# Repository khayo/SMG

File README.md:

# SMG - Sistema de Monitoramento de Geradores

## Introdução

Projeto de conclusão de curso dos alunos do curso de eletroeletrônica da ETEC Lauro Gomes

## Integrantes
* Caio Pavan Lima dos Santos
* Guilheme Gil Farias Sousa
* Gustavo Vinícius de Oliveira Barros
* Khayo Vannucci Rodrigues
* Lucas Barros Silva

## Sobre o Projeto
Trata-se de um hardware de automação de geradores, tanto a parte física (placas e componente), quanto a parte lógica (software de controle) foram desenvolvidas por nós.

## Microcontrolado
Está sendo utilizadado o PIC18F4550, poís além de possuir uma grande quantidade de portas lógicas e alta velocidade de processamento (até 48mHz), possui suporte a comunicação USB, o que pode simplificar updates de Firmware no futuro.

## IDE
A IDE selecionada para desenvolver o projeto foi o MikroC devido a familiaridade dos membros com a ferramenta e a abundância de material disponível para consulta.

## Projeto Virtual
Para simulações está sendo utilizado o Software Proteus, também escolhido devido a familiaridade dos membros com a ferramenta.

## Projeto Físico
O Hardware está sendo desenvolvido em protoboard e após realização de testes de funcionamento, será montado em placa de circuito impresso.

## Monografia
Também está disponivel neste repositório a monografia, por onde mostraremos os passos do desenvolvimento do projeto.

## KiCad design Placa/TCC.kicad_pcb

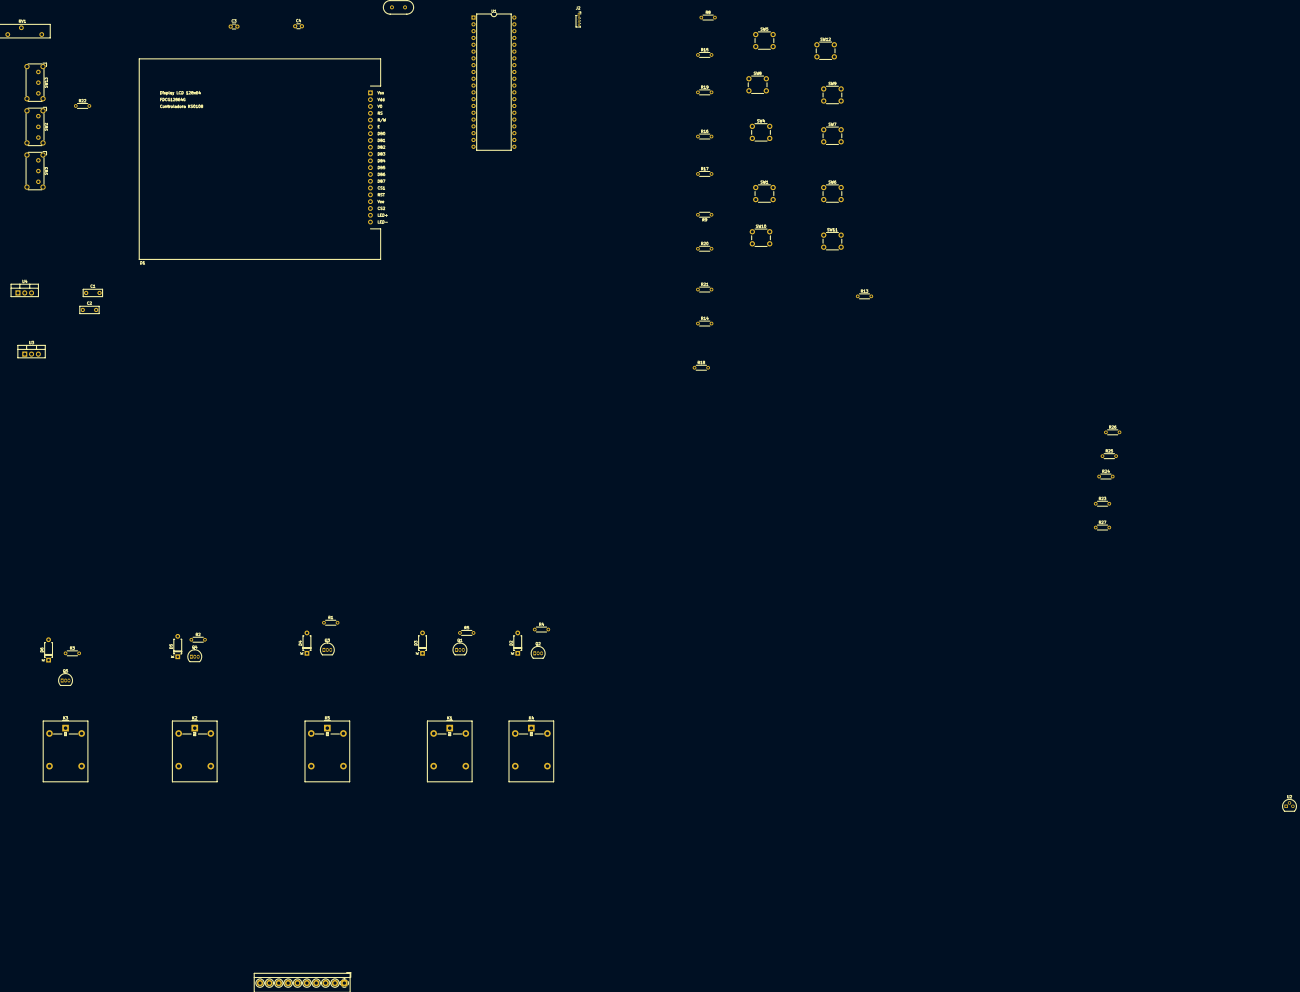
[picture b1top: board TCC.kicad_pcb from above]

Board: 2 copper layers, 63 parts (0 on the bottom side), 69 nets, no tracks yet.

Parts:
C1, C2: 10n; C_Rect_L7.0mm_W2.5mm_P5.00mm
C3, C4: 22p; C_Disc_D3.0mm_W1.6mm_P2.50mm
D1: FDCG12864; FDCG12864G
D2, D3, D4, D5, D6: DIODE; D_A-405_P7.62mm_Horizontal
J1: Screw_Terminal_01x10; TerminalBlock_4Ucon_1x10_P3.50mm_Horizontal
J2: Conn_01x05_Female; PinSocket_1x05_P1.00mm_Vertical
K1, K2, K3, K4, K5: G5LE-1; Relay_SPDT_Omron-G5LE-1
Q1, Q2, Q3, Q4, Q5: BC548; TO-92_Inline
R1, R2, R3, R4, R5, R16: 4700; R_Axial_DIN0204_L3.6mm_D1.6mm_P5.08mm_Horizontal
R8: 3300R; R_Axial_DIN0204_L3.6mm_D1.6mm_P5.08mm_Horizontal
R9: 2200R; R_Axial_DIN0204_L3.6mm_D1.6mm_P5.08mm_Horizontal
R13, R25, R26: 1000; R_Axial_DIN0204_L3.6mm_D1.6mm_P5.08mm_Horizontal
R14: 10000; R_Axial_DIN0204_L3.6mm_D1.6mm_P5.08mm_Horizontal
R15: 6800; R_Axial_DIN0204_L3.6mm_D1.6mm_P5.08mm_Horizontal
R17: 3900; R_Axial_DIN0204_L3.6mm_D1.6mm_P5.08mm_Horizontal
R18: 680; R_Axial_DIN0204_L3.6mm_D1.6mm_P5.08mm_Horizontal
R19: 470; R_Axial_DIN0204_L3.6mm_D1.6mm_P5.08mm_Horizontal
R20, R22: 220; R_Axial_DIN0204_L3.6mm_D1.6mm_P5.08mm_Horizontal
R21: 33; R_Axial_DIN0204_L3.6mm_D1.6mm_P5.08mm_Horizontal
R23: 100000; R_Axial_DIN0204_L3.6mm_D1.6mm_P5.08mm_Horizontal
R24: 33000; R_Axial_DIN0204_L3.6mm_D1.6mm_P5.08mm_Horizontal
R27: 27000; R_Axial_DIN0204_L3.6mm_D1.6mm_P5.08mm_Horizontal
RV1: R_POT; Potentiometer_Bourns_3006P_Horizontal
SW1, SW4, SW5, SW6, SW7, SW8, SW9, SW10, SW11, SW12: SW_Push_Dual; SW_PUSH_6mm_2_Contatos
SW2, SW3, SW13: SW_Push_SPDT; SW_E-Switch_EG1224_SPDT_Angled
U1: PIC18F4550-IP; DIP-40_W15.24mm
U2: LM35-LP; TO-92
U3: L7805; TO-220-3_Vertical
U4: L7812; TO-220-3_Vertical
Y1: Crystal; Crystal_HC18-U_Vertical

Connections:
5V: C1.1, C2.1, D1.2, D2.2, D3.2, D4.2, D5.2, D6.2, R8.1, R9.1, R14.2, R15.2, R16.2, R17.2, R18.2, R19.2, R20.2, R21.2, R22.1, SW3.2, SW13.2, U1.11, U1.32, U3.3
12V: K1.5, K2.5, K3.5, K4.5, K5.5, U4.3
+12V: R26.1, U3.1, U4.1
LED+: D1.19, SW2.2
MCLR: J2.1, U1.1
unnamed: Q1.2, R5.1
unnamed: Q2.2, R4.1
unnamed: Q3.2, R1.1
unnamed: Q4.2, R2.1
unnamed: Q5.2, R3.1
unnamed: R8.2, SW1.2
unnamed: R9.2, SW11.2
unnamed: R14.1, SW6.2
unnamed: R15.1, SW5.2
unnamed: R16.1, SW4.2
unnamed: R17.1, SW7.2
unnamed: R18.1, SW10.2
unnamed: R19.1, SW9.2
unnamed: R20.1, SW12.2
unnamed: R21.1, SW8.2
unnamed: R22.2, SW2.1
unnamed: R23.1, R27.2
unnamed: R23.2, R24.2
unnamed: R24.1, R25.1
unnamed: R25.2, R26.2
OSC1: C4.1, U1.13, Y1.1
OSC2: C3.1, U1.14, Y1.2
PGC: J2.4, U1.39
PGD: J2.3, U1.40
PGM: D1.16, J2.5, U1.38
R1T1: J1.1, K4.1
R1T3: J1.2, K4.3
R2T1: J1.3, K1.1
R2T3: J1.4, K1.3
R3T1: J1.5, K5.1
R3T3: J1.6, K5.3
R4T1: J1.7, K2.1
R4T3: J1.8, K2.3
R5T1: J1.9, K3.1
R5T3: J1.10, K3.3
RA1: R13.1, SW1.1, SW4.1, SW5.1, SW6.1, SW7.1, SW8.1, SW9.1, SW10.1, SW11.1, SW12.1, U1.3
RA3: R4.2, U1.5
RA4: R5.2, U1.6
RA5: R1.2, U1.7
RB0: D1.15, U1.33
RB1: D1.18, U1.34
RB2: D1.4, U1.35
RB3: D1.5, U1.36
RB4: D1.6, U1.37
RC2: SW3.1, U1.17
RD0: D1.7, U1.19
RD1: D1.8, U1.20
RD2: D1.9, U1.21
RD3: D1.10, U1.22
RD4: D1.11, U1.27
RD5: D1.12, U1.28
RD6: D1.13, U1.29
RD7: D1.14, U1.30
RE0: R2.2, U1.8
RE1: R3.2, U1.9
RE2: SW13.1, U1.10
T1: D2.1, K4.2, Q2.1
T2: D3.1, K1.2, Q1.1
T3: D4.1, K5.2, Q3.1
T4: D5.1, K2.2, Q4.1
T5: D6.1, K3.2, Q5.1
V0: D1.3, RV1.2
VEE: D1.17, RV1.1
VSS: C1.2, C2.2, C3.2, C4.2, D1.1, D1.20, J2.2, Q1.3, Q2.3, Q3.3, Q4.3, Q5.3, R13.2, R27.1, U1.12, U1.31, U3.2, U4.2

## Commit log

2019-09-28 Primeiro envio dos arquivos
2019-09-28 Adicionado arquivo README.md
2019-09-28 teste de commit feito pelo lucfoxxd
2019-09-29 Corrigido marcação do arquivos
2019-09-29 correção de erros de grafia
2019-09-29 Instrução para dar aula.
2019-09-29 Alterado o arquivo readme para sua versão correta.
2019-09-29 Adicionado arquivo da monografia.
2019-09-29 Alterado para conter a prova final do lucas
2019-09-29 Conclusão da prova do Lucas.
2019-09-29 Alterado arquivo readme com erros ortográficos.
2019-09-29 correção dos erros de ortografia do arquivo README.md
2019-09-29 Primeira versão do arquivo contendo alterações pendentes.
2019-09-29 Update Alterações_pendentes.docx
    Removido sensor de frequência e pressão da monografia
2019-09-29 teste do docx2txt e alteração do nome dos arquivos para evitar erro
2019-09-29 teste de git, sem pasta attibutes
2019-09-29 teste de git sem docx2txt pelo notebook
2019-09-29 Arquivo de aula git
2019-09-29 texto de teste no aula_git guilherme
2019-09-29 texto de teste no aula_git gustavo
2019-09-29 texto de teste do aula_git Caio
2019-09-29 dicionei uma linha inutil
2019-09-29 inserido GOKU
2019-09-29 ateste para dar merge
2019-09-29 utro ero para ser arrumado
2019-09-29 inserido 1010
2019-09-29 teste alteração docx sem docx2txt pc guilherme
2019-09-29 apagado arquivos de projeto desnecessários
2019-09-29 apagado todos os nomes d arquivo
2019-09-29 adicionado muralha demilich solar
2019-09-29 adicionado templo forja
2019-09-29 adicionado colosso tarrasque
2019-09-29 apagado o nome das cartas
2019-09-29 adicionado luffy zoro
2019-09-29 adicionado nami sanji
2019-09-29 adicionado robin usopp
2019-09-29 troque uma carta
2019-09-29 adicionado paladino e troll
2019-09-29 adicionado esqueleto e vikkings
2019-09-29 apagado nomes one piece
2019-09-29 adicionado goku raditz
2019-09-29 adicionado vegeta nappa
2019-09-29 adicionado ace
2019-09-29 adicionado shanks
2019-09-30 adicionado led diodo
2019-09-30 adicionado zenner capacitor
2019-09-30 adicionado resistor capacitor
2019-09-30 adicionado trimpot trimmer
2019-09-30 adicionado diac transistor
2019-09-30 adicionado ldr triac
2019-09-30 adicionado boa hankok
2019-10-01 Ajustado calculo de temperatura do LM35
2019-10-01 Adicionada planilha de custos a pasta monografia
2019-10-02 Alterado nome d arquivo para nao conter espaços
2019-10-02 Teste do xlsx txt
2019-10-02 teste script
2019-10-02 teste
2019-10-02 teste depois de reiniciar
2019-10-02 corrigida valor da planilha de custo
2019-10-03 Adicionado folheto de apresentação do módulo
2019-10-03 Adicionado gitignore
2019-10-03 Adicionado git ignore em cada pasta
2019-10-03 Alterado gitignore da pasta proteus
2019-10-03 Configuração final do gitignore
2019-10-03 Adicionado reles de pre-aque, partida, sol. combustivel
2019-10-06 Adicionada extesão .ini ao git ignore
2019-10-06 Enviada primeira versão do fluxograma de funcionamento do gmg
2019-10-06 Adicionado e reorganizado botões do painel do modulo
2019-10-06 inserido layout do painel frontal
2019-10-06 adicionado layout do pinel frontal 2
2019-10-06 correção layout do painel frontal
2019-10-06 Atualizado conteúdo: sensor de temp, drive e correções.
2019-10-06 Alterada pasta layout e folheto para estarem na raiz do repositório
2019-10-06 Adicionado lógica para os botões novos reset, manual, auto, parte, parar
2019-10-07 Ajustado funcionamento dos botões do teclado do módulo
2019-10-07 Layout frontal do módulo feito pelo Lucas.
2019-10-07 gitignore da raiz restaurado
2019-10-07 Ajustado linhas tortas e adicionado função de manual e automatico
2019-10-08 criação das pastas para desenvolvimento do banner
2019-10-08 imagens e texto prévio para o tópico "proteus" do banner
2019-10-09 Adicionado Pasta teclado
2019-10-09 Alterações feitas no layout do teclado
2019-10-09 adicionado atualização de trilhas
2019-10-09 teclado com layout corrigido
2019-10-09 Alterada trilha torta do botão partir
2019-10-09 Alterado nome do arquivo para nao conter espaço
2019-10-09 Teclado finalizado e revisado. Closes #3.
2019-10-10 Corrigido posição e funcionamento da função de calibração
2019-10-10 Alterações no commit anterior. #7
2019-10-12 Alterada porta do sensor vcc de AN3(5) para AN2(4)
2019-10-12 Ajuste do calculo de temperatura
2019-10-12 Corrigido valores do divisor de tensão so sensor vcc
2019-10-12 Correção do calculo de VCC. #7
2019-10-12 adicionado pasta placa_tela_tecaldo.#6
2019-10-12 Corrigido código para que o valor de temperatura não pisque. #7
2019-10-12 Desativei temporariamente as funções de comunicação serial #7
2019-10-12 Correção da tensão de entrada do sensor de Vcc
2019-10-12 atualização do layout da placa tela teclado V2.#6
2019-10-12 removido pasta teclado
2019-10-12 deletada a pasta tela teclado.#6
2019-10-12 removido códigos da interface serial. #7
2019-10-12 removido mais entradas que se comunivacam por serial. #7
2019-10-12 Adequação do simulador para nova disposição das portas. #7
2019-10-12 Melhoria na distribuição dos itens. #7
2019-10-12 melhoria na legibilidade do código. #7
2019-10-12 legibilidade e testes nos reles (pre, part, sole). #7
2019-10-12 alteração nas portas analógicas an0 até an3 >> an0 até an2. #7
2019-10-12 alterado local onde o calculo do sensor de temp. é corrigido #7
2019-10-12 correção do arquivo git ignore
2019-10-12 adicionado teclado tela layout.#6
2019-10-12 Adicionada rotinas para pre-aquecimento. #7
2019-10-12 retirado códigos desnecessários referente a Vca. #7
2019-10-12 Removido códigos desnecessários referentes a Vca. #7
2019-10-13 adicionada rotinas de funcionamento auto/manual. #7
2019-10-13 Adicionado indicador de modo (manual / Auto). #7
2019-10-13 adicionado rotina para ligar e desligar solenoide de combustivel. #7
2019-10-13 Adicionada rotina de motor de partida. #7
2019-10-13 Adicionada rotinas de partida e parada de GMG. #7
2019-10-13 Adicionado variavel de status do gerador. #7
2019-10-13 Adicionado controles e condiçoes de partida do motor. #7
2019-10-13 Adicionado rotina de desligamento do pre-aquecimento na partida. #7
2019-10-13 atualização do layout da placa tela/teclado.#6
2019-10-14 Adicionado mais atividades desenvolvidas e atualizadas.
2019-10-14 Teclado e display, ligaçoes ok, necessário melhorias. #6
2019-10-14 Corrigido trilhas. #6
2019-10-14 Adicionado Layout Frontal do Módulo.
2019-10-14 Inicio do desenvolvimento do monitor de energia. #7
2019-10-14 Adicionado layout frontal com medidas reais do módulo.
2019-10-14 Deletado layouts antigos feitos do módulo.
2019-10-14 Fonte de edição do layout em tamanho real.
2019-10-14 Adicionado fonte do layout frontal do módulo.
2019-10-14 Adicionado fonte do layout frontal do modulo.
2019-10-14 Adicionado fonte de edição do layout em tamanho real.
2019-10-14 Correção dos arquivos do layout.
2019-10-14 Adicionado layout frontal para visualização.
2019-10-14 Enviando corrente via serial somente quando solicitado. #7
2019-10-14 Teclado certo
2019-10-15 Adicionado e finalizado o banner (Arquivo fonte)
2019-10-15 Adicionado e fizalizado o banner (Arquivo para visualização)
2019-10-15 adicionado trimpot na placa tela/teclado.#6
2019-10-16 Correção de trilhas do trimpot. #6
2019-10-27 Revisão da placa do telcado para impressão #7
2019-10-27 Versão final para impressão da PCI, com ilhas alteradas. #7
2019-10-27 Ultima versão com trilha alterada. Pronto para impressão. #7
2019-10-28 Trilhas mais largas, jumpers no trimpot. #7
2019-10-28 Adicionado furos guia. #7
2019-10-28 Corrigida a data e versão do hardware. #7
2019-10-31 Corrigidas marcas de alinhamento. #7
2019-11-02 Adcionado conteúdos que etão pendentes (Parte 1/2)
2019-11-02 Adicionado conteúdos que estão pendentes (Parte 1/2).
2019-11-02 Adicionado conteúdos que estavam pendentes (Parte 2/2).
2019-11-02 Corrigido o nome do Guilherme no arquivo: principal da monografia.
2019-11-15 monitoramento de falha BVT. #7
2019-11-15 retorno de rede implementado; #7
2019-11-21 Placa de reles das saídas. #7
2019-11-23 Adicionado conteúdos atualizados da construção do módulo.
2019-11-23 Adicionado conteúdo sobre módulo controlador de gerador.
2019-11-23 Adicionado conteúdo: layout do teclado, painel de contato.
2019-11-25 teclado sem visor. #7
2019-11-26 Adicionado conteúdos semi finais da monografia.
2019-11-27 versão do código finalizada para apresentação. #7
2019-12-24 Arquivos de projeto da PCI
2019-12-24 Reorganização dos arquivos
2019-12-24 Apagado arquivos usados para ensinar o uso do git/github
